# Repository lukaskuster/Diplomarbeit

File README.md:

# P2P GSM-Telephone-Gateway with Client App

### Diploma thesis by [Lukas Kuster](https://github.com/lukaskuster) and [Quentin Wendegass](https://github.com/quentinwendegass) at HTL Mössingerstraße - 4th April 2019

## Table of contents

- [Abstract](#abstract)
  - [Assignment of Tasks](#assignment-of-tasks)
  - [Implementation](#implementation)
  - [Results](#results)
- [Authors](#authors)
- [License](#license)
- [Links](#links)

## Abstract

People that are travelling in foreign countries and still want to be able to use their phone number from their home country, often have to expect huge roaming costs. Because of that, a user-friendly device equipped with the SIM card of the local carrier will be developed, that can then be placed locally in that country. This device will then be able to receive phone calls and SMS via the local carrier and transmit it through a direct Peer-to-peer connection over the internet to the end-user using a client app. Meanwhile the whole process should look and feel like a real, normal call.

### Assignment of Tasks

Because the data transfer rates that accumulate through the voice band streams are relatively big, the transfer has to happen directly between the gateway and the client, with only minimal interaction of a third party (server). The whole system should be designed as easy as possible, so that the setup consists only of starting up the device, quickly running through a setup in the client app and being able to use the gateway instantaneously.

### Implementation

The system basically consists of three components: the gateway, which establishes the calls and SMS messages through its GSM module and the client app, which enables the user to initiate/answer these calls and messages, as well as providing the option to change several settings. In addition, there is a Rendezvous- or Signaling-Server, which initiates the direct peer- to-peer connection between the client and the gateway, as well as the user management of the whole platform which provides the needed scalability.

### Results

The diploma thesis will show, whether such a product is technically as well as economically viable. While working on this project the whole software for such a product as well as a hard- ware prototype will be established.

## Authors

- **Quentin Wendegass** - _Gateway Software & Server_ - [Website](https://wendegass.com)

- **Lukas Kuster** - _Gateway Hardware & iOS-Client_ - [Website](https://lukaskuster.com)

## License

This project is licensed under the GNU Affero General Public License - see the [LICENSE](LICENSE) file for details

## Links

- [iOS-Client: SIMplePhoneKit Documentation](https://lukaskuster.github.io/Diplomarbeit/code-docs/client-ios/) 
- [Gateway: gatewayw Documentation](https://quentinwendegass.github.io/Diplomarbeit/code-docs/gatewayw/html/) 

* [Lukas' repo (@lukaskuster/Diplomarbeit)](https://github.com/lukaskuster/Diplomarbeit)
* [Quentin's repo (@quentinwendegass/Diplomarbeit)](https://github.com/quentinwendegass/Diplomarbeit)

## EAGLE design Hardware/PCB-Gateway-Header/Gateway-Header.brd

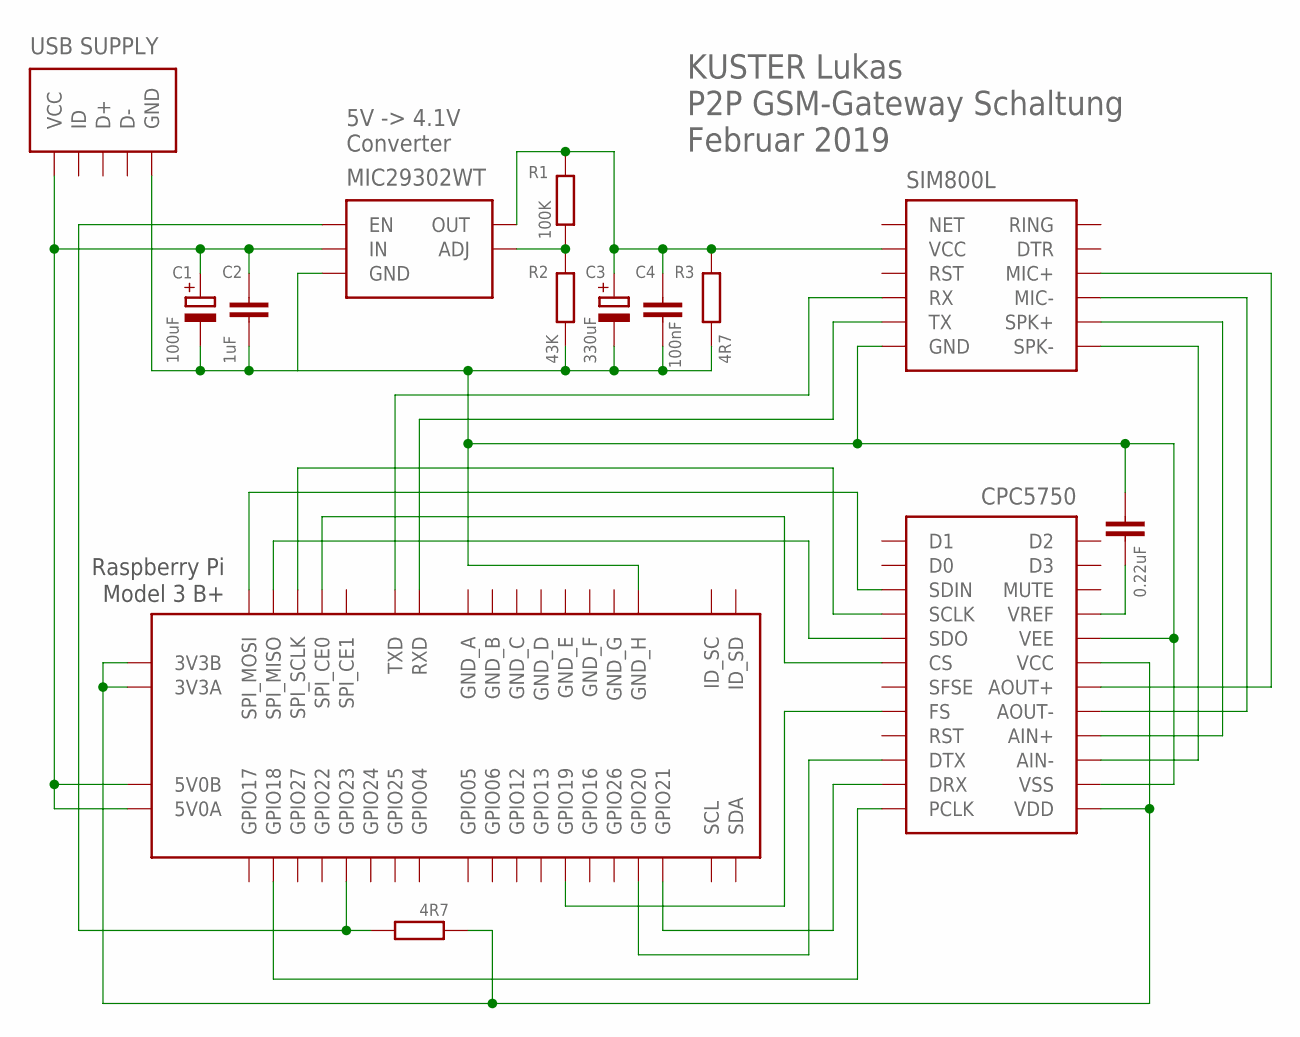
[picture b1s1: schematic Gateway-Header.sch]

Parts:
C: 0.22uF; C025-025X050
C1: 100uF; B45181B
C2: 1uF; C025-025X050
C3: 330uF; B45181B
C4: 100nF; C025-025X050
IC2: MIC29302WT; TO254P483X1022X1511-5P
R1: 100K; 0204/7
R2: 43K; 0204/7
R3, R5: 4R7; 0204/7
U$4: CPC5750
U$5: SIM800LMODULE
U$6: ZX62D-B-5P8-JUNK; ZX62D-B-5P8
X1: RASPI_BOARD_B+#_H; RASPI_BOARD_B+HAT

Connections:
+3.3V: R5.2, U$4.V_CC (VCC), U$4.V_DD (VDD), X1.1 (3V3A), X1.17 (3V3B)
+4V: C3.+, C4.2, IC2.4 (OUT), R1.2, R3.2, U$5.VCC
+5V: C1.+, C2.2, IC2.2 (IN), U$6.P$1 (VCC), X1.2 (5V0A), X1.4 (5V0B)
GND: C.2, C1.-, C2.1, C3.-, C4.1, IC2.3 (GND), R2.1, R3.1, U$4.V_EE (VEE), U$4.V_SS (VSS), U$5.GND, U$6.P$5 (GND), X1.39 (GND_H)
GND_A: X1.6 (GND_A)
GND_B: X1.9 (GND_B)
GND_C: X1.14 (GND_C)
GND_D: X1.20 (GND_D)
GND_E: X1.25 (GND_E)
GND_F: X1.30 (GND_F)
GND_G: X1.34 (GND_G)
unnamed: U$5.RX, X1.8 (TXD)
unnamed: U$5.TX, X1.10 (RXD)
unnamed: IC2.5 (ADJ), R1.1, R2.2
unnamed: U$4.A_IN- (AIN-), U$5.SPK-
unnamed: U$4.A_IN+ (AIN+), U$5.SPK+
unnamed: U$4.A_OUT- (AOUT-), U$5.MIC-
unnamed: U$4.A_OUT+ (AOUT+), U$5.MIC+
unnamed: C.1, U$4.V_REF (VREF)
unnamed: U$4.CS, X1.24 (SPI_CE0)
unnamed: U$4.SCLK, X1.23 (SPI_SCLK)
unnamed: U$4.SDIN, X1.19 (SPI_MOSI)
unnamed: U$4.SDO, X1.21 (SPI_MISO)
unnamed: U$4.PCLK, X1.12 (GPIO18)
unnamed: U$4.D_RX (DRX), X1.40 (GPIO21)
unnamed: U$4.D_TX (DTX), X1.38 (GPIO20)
unnamed: U$4.FS, X1.35 (GPIO19)
unnamed: IC2.1 (EN), R5.1, X1.16 (GPIO23)

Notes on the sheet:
KUSTER Lukas P2P GSM-Gateway Schaltung Februar 2019
5V -> 4.1V Converter

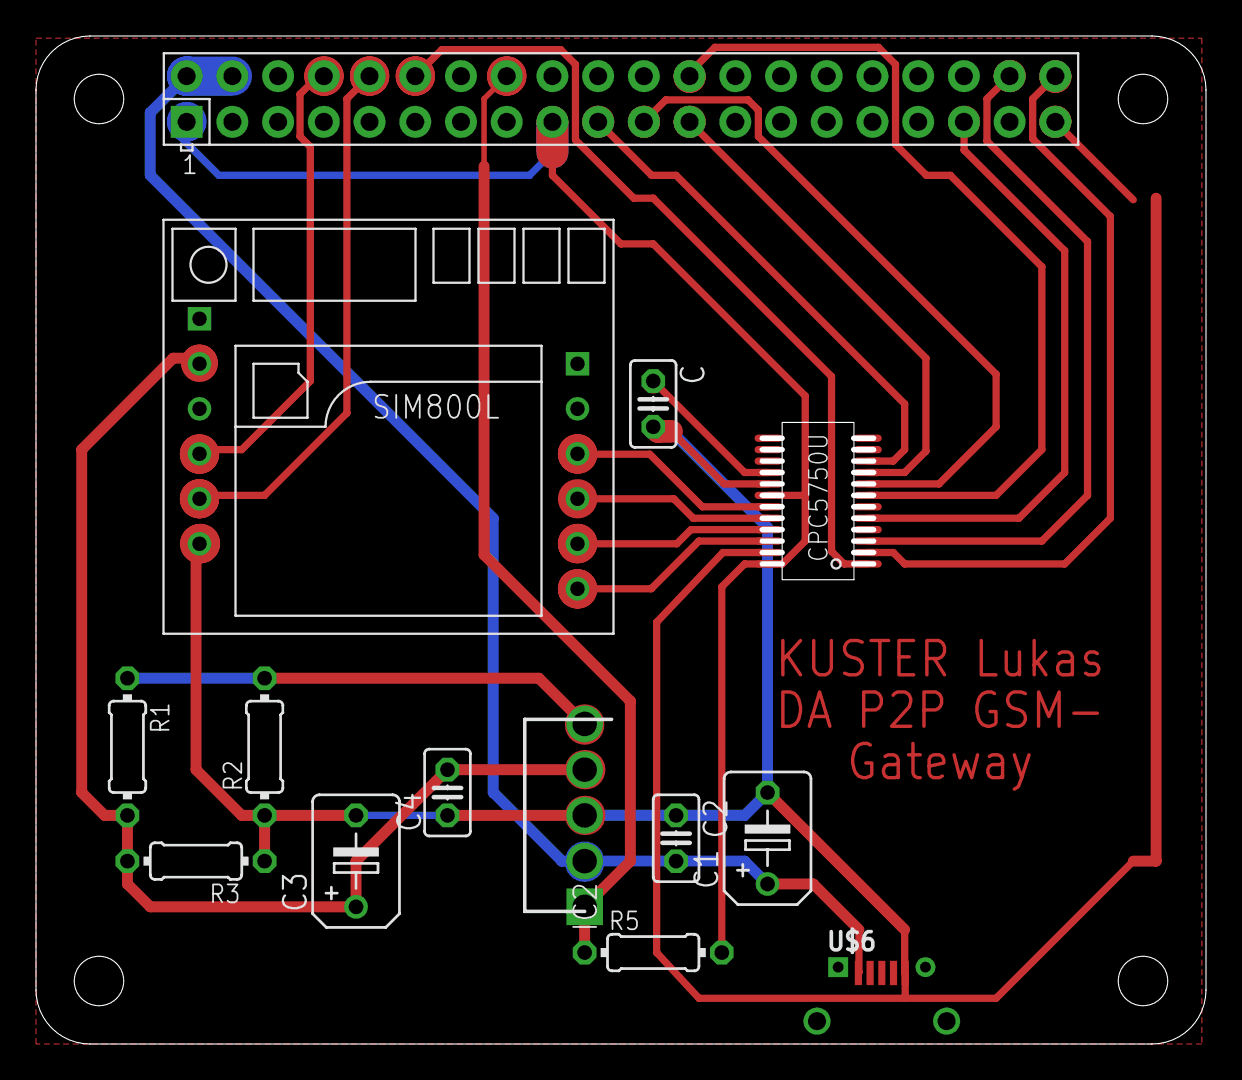
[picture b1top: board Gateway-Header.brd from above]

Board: 2 copper layers, 64.7 x 55.7 mm, 14 parts (0 on the bottom side), 21 nets.

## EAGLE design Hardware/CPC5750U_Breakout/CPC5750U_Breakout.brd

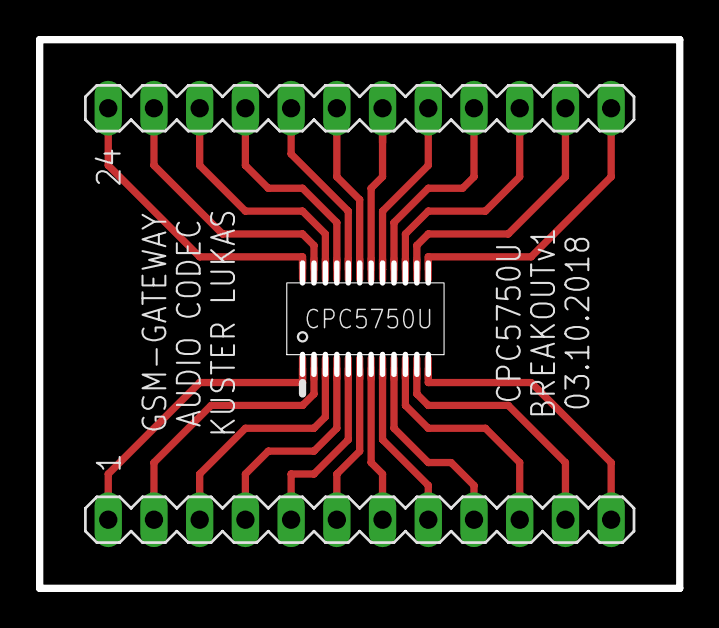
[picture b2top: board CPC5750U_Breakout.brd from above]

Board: 2 copper layers, 35.6 x 30.5 mm, 3 parts (0 on the bottom side), 24 nets.

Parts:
BTM: MA12-1
E$1: CPC5750
TOP: MA12-1

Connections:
S$2: E$1.V_SS, TOP.2
S$3: E$1.A_IN-, TOP.3
S$4: E$1.A_IN+, TOP.4
S$5: E$1.A_OUT-, TOP.5
S$6: E$1.A_OUT+, TOP.6
S$7: E$1.V_CC, TOP.7
S$8: E$1.V_EE, TOP.8
S$9: E$1.V_REF, TOP.9
S$10: E$1.MUTE, TOP.10
S$11: E$1.D3, TOP.11
S$12: E$1.D2, TOP.12
S$13: BTM.1, E$1.PCLK
S$14: BTM.2, E$1.D_RX
S$15: BTM.3, E$1.D_TX
S$16: BTM.4, E$1.RST
S$17: BTM.5, E$1.FS
S$18: BTM.6, E$1.SFSEL
S$19: BTM.7, E$1.CS
S$20: BTM.8, E$1.SDO
S$21: BTM.9, E$1.SCLK
S$22: BTM.10, E$1.SDIN
S$23: BTM.11, E$1.D0
S$24: BTM.12, E$1.D1
S$26: E$1.V_DD, TOP.1

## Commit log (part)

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2018-04-19 added documentation stuff
2018-04-20 adding gantt-diagramm + aufgabestellung
2018-04-20 added docu
2018-04-23 changes to GANTT diagram
2018-04-23 changed documentation
2018-04-26 Adding Presentation
2018-04-26 changes to Dokumentation
2018-09-18 Add server libraries
2018-09-21 Add test script for sim800l module
2018-09-21 Change stuff
2018-09-21 Add Sim800 wrapper class
2018-09-22 Code cleanup and add possibility for custom command
2018-09-24 Close sim module after program finish
2018-09-25 Modify serial connection
2018-09-25 Add name and error message to event
2018-09-26 Split sim800 in different files and create a module
2018-09-26 Fix spelling mistakes
2018-09-26 Switch to pipenv
2018-09-26 Change directory structure
2018-09-26 Add deploy script
2018-09-28 Add support for sending sms
2018-10-02 Add readme
2018-10-03 HW: add CPC5750U breakout board
2018-10-09 client-ios: generate xcode project
2018-10-09 basic UI structure + app icon
2018-10-11 Add SMS-Test
2018-10-11 Fix command to end with ctrl + c
2018-10-11 Caught error when wrong bites get transmitted
2018-10-11 Change host
2018-10-11 Add PdSP-Diagram
2018-10-16 Add signaling-server structure
2018-10-16 Add api template
2018-10-16 Change PdSP chart
2018-10-17 Add authentication
2018-10-18 current app state
2018-10-18 Add signaling server
2018-10-18 Add signaling test
2018-10-18 improvements in voicemail tab / add framework for networking/signalling
2018-10-19 Add database functionality to the signaling server
2018-10-19 Update host
2018-10-19 Add deploy script and change worker filenames
2018-10-19 Code cleanup
2018-10-20 Add gateway endpoint
2018-10-22 Change signaling method
2018-10-22 Add webrtc test with signaling server
2018-10-22 Add gateway api enpoints to paw
2018-10-23 Add api endpoints
2018-10-23 Update response values + put endpoint for gateway
2018-10-23 changes to voicemail functionality / implemented signaling & rtc support (not working yet)
2018-10-24 Fix offer and answer packet
2018-10-24 Fix pip8 errors
2018-10-24 Add error messages
2018-10-24 Add stun server
2018-10-24 rtc setup now possible (RTCClient needs to be redesigned)
2018-10-25 Add logging + bug fixes and code cleanup
2018-10-25 Pip8 fixes
2018-10-25 Add doc comments
2018-10-25 Small code improvements
2018-10-26 Add sse functionality
2018-10-27 Add error handling for failed stream requests
2018-10-27 Change host and add needed header for nginx
2018-10-30 UI tweaks and functionality for ContactTableViewController
2018-10-30 fix iPad crash due to missing property for UIAlertController
2018-11-06 Create Level and AnsiEscapeSequence not in Logger
2018-11-07 SPManager / data models / recent calls view
2018-11-08 Add device endpoints + auth fix
2018-11-08 APIClient: registerDeviceWithServer/getAllGateways
2018-11-09 Update error messages and reformat code
2018-11-09 Add authorization errors
2018-11-09 several API client implementations
2018-11-10 Add authenticate endpoint
2018-11-10 Change response at authentice endpoint
2018-11-10 added authentication logic
2018-11-10 potential fix to iCloud sync problem (issue #6)
2018-11-10 Some improvements and log modules
2018-11-10 Add call module and main entry point
2018-11-12 adds hangUp as pushToGateway Event
2018-11-12 fix local keychain problem when signing in with iCloud
2018-11-12 Sim800 module update + fixes
    + Renamed emitted events to camel case
    + Add ATCommand Class
    + Update ATEvent Class
    + Add sim800 response objects
    + Echo mode can be disables in serial loop
    + Refactored sim800 class to parse response values
2018-11-13 improved login/register ViewController UI also includes register functionality, which still needs some API changes
2018-11-13 removes unused function
2018-11-13 Sync fix
    + new delete /devices endpoint #6
    + fix device return parameters
    + add firstName and lastName arguments to post device
    + Add sync to device #6
2018-11-13 Add async support and response parser
2018-11-13 fixed create account logic after API change (now stable)
2018-11-14 Get imei on first start
2018-11-14 Add new at-commands
2018-11-14 Add cloudUserId
2018-11-15 improvements to iCloud keychain sharing (issue #6)
2018-11-16 Add endpoints for device push notifications
2018-11-19 changed event API endpoint
2018-11-20 Fix apn notifications
2018-11-21 error messages on LoginView
2018-11-21 outsourcing CloudEnvironmentButton
2018-11-22 Implement push notifications for device
2018-11-23 Changes
    + Better WebRTC implementation
    + Signaling timeout fix
    + Add config wrapper
    + Disable echo on sim800 module if it runs in debug mode
    + More small bug fixes
2018-11-24 Fix signaling bug
2018-11-29 Add parser functionality + Code cleanup
2018-11-30 Add ice canditate exchange to gateway
2018-11-30 Optimize for raspberry
2018-12-10 Add caller identification on ring event
2018-12-12 Changes project to use cython
2018-12-12 Adds carrier and firmware version to gateway model
2018-12-12 Uses absolut config path
2018-12-14 Modifies sim800 setup
2018-12-14 Adds scheduler module
2018-12-17 Clean up project
2018-12-17 Add competition applications
2018-12-30 Adds pcm driver
2018-12-30 Fixes config loading bugs
2018-12-30 Changes version to 0.0.3
2018-12-31 Changes char device interface to use 8bit samples
2019-01-01 Adds install scripts
2019-01-01 Adds test for pcm library/driver
2019-01-01 Adds pcm library
2019-01-02 Renames functions and cleans up header
2019-01-02 Changes webrtc to use the pcm wrapper
2019-01-02 Adds possibilities to build the source
2019-01-02 Sets the properly frame length
2019-01-02 Adds requirenments.txt
2019-01-02 Changes version to 0.1.0
2019-01-03 Updates deployment script
2019-01-03 Renames test and fixes Makefile
2019-01-03 Implements split_str() in C
2019-01-03 Removes unused cython declarations
2019-01-04 Fixes webrtc closing bug and optimizes test
2019-01-07 Updates documentation
2019-01-09 Adds color property to gateway
2019-01-09 Further Improvements to Settings View + separate view for name change + set color functionality fully working + order gateway menu button
2019-01-10 more settings UI stuff + disable bouncing on color/name view + grey borders for name textfield + autolayout in colorselector + updated sketch file for icons used
2019-01-10 added TODO file
2019-01-10 added gateway change SIM Pin UI
2019-01-10 total UI support for gateway firmware update
2019-01-14 WebRTC codec selection workaround + move test to specific gateway
2019-01-16 Fixes sim800 bugs
2019-01-16 Changes webrtc to emit errors
2019-01-16 Adds sim800 tests
2019-01-18 Implements voip push notifications
2019-01-19 Adds new push events
2019-01-19 better approach to WebRTC codec selection (still not perfect)
2019-01-19 add select gateway modal on call init in contacts
2019-01-19 adds a lot of CallKit related stuff (incoming calls are now supported and displayed accordingly)
2019-01-20 Implements new events
2019-01-20 fix bug that prevented CallKitManager.reportCallEnded()
2019-01-20 Fixes apn bugs
2019-01-20 lots of changes regarding call handling and a basic Call UI
2019-01-21 fixed PCMAonly bug + deinit peerconnection improvement
2019-01-21 Adds timeout on receiving frame
2019-01-21 Adds dtmf tone support
2019-01-21 Add project website for projects.htl-klu.at
2019-01-21 project website: change from structure.svg to .pdf (font problem)
2019-01-22 Adds implementation and template for answer and hold call
2019-01-22 Fixes bug
2019-01-22 Implements better error handling
2019-01-22 Handles sse errors
2019-01-22 Implements reconnecting to sse server
2019-01-22 Implements reconnect event to notice a connection lost
2019-01-23 add sexy pic of Rodiga
2019-01-25 Adds custom aiortc package to the project
2019-01-25 Fixes logging bug
2019-01-25 Modifies setup to don't use the deprecated dependency_links option
2019-01-25 Removes cython from requirements
2019-01-25 Changes version to 0.1.1
2019-01-25 Updates depoly script
2019-01-30 Fixes typo
2019-01-30 Adds gateway authentication at signaling process
2019-02-01 complete refactor of WebRTCClient & SignalingClient (calls are now working!)
2019-02-01 Fixes bug when no ice candidates are received
2019-02-02 rename SettingsGatewayChangeSIMPinViewController -> GatewaySIMPinViewController
2019-02-02 add FancyBounceVCAnimation (forgot file in commit 0c0669c)
2019-02-02 Adds initial ble setup program
2019-02-02 Adds pcm driver and setup program
2019-02-04 Adds install scripts and modifies deploy script
2019-02-05 Restructures project to setup the build process
2019-02-05 Adds c libs that mistakenly were not commited
2019-02-05 Adds docs for gatewayw
2019-02-06 Adds build script and systemd service units
2019-02-06 Changes script to use environment variables
2019-02-06 Adds installation scripts
2019-02-07 Sets threads in daemon mode
2019-02-07 Updates logging module to use config file
2019-02-07 Adds log config to build
2019-02-08 Adds user service and ble configuration
2019-02-08 Handles check for pin status
2019-02-15 current ble setup state
2019-02-15 fix app icon
2019-03-04 Adds Dialpad (UI & Functionality)
2019-03-05 Recent Calls View Refinements
2019-03-05 getting rid of unused stuff in Contacts View
2019-03-05 visual fix on recent calls view
2019-03-06 syncing SPGateways with Realm
2019-03-06 fix UIAlert popovers on iPad in voicemails
2019-03-06 fix delete voicemail bug
2019-03-06 fix dialpad phone icon tint color
2019-03-06 hide call duration if not even connected in recent calls
2019-03-08 complete refactor of ChatTableViewController (objc -> swift)
2019-03-08 adds UIAlertController when deleting chat
2019-03-14 Fixes bugs and code cleanup
2019-03-14 Changes documentation
2019-03-14 Changes version to 0.2.0
2019-03-14 Updates Readme (second try)
2019-03-27 refactoring to support thesis documentation
2019-04-01 adds jazzy documentation for iOS-Client
2019-04-01 fixing BLE compatibility issues
2019-04-01 fix weekday bug (maybe working idk)
2019-04-01 HW: add gateway header pcb
2019-04-01 cross-referencing each others repository
2019-04-01 change /docs structure
2019-04-01 hide all the html/css stuff to linguist
2019-04-01 fixing mistake that happend while changing docs folder structure
2019-04-01 adds documentation for the ios-client (at least 50%)
2019-04-01 add ios-client doc coverage badge to readme
2019-04-02 Create LICENSE
2019-04-02 Adds gatewayw html doc and code coverage report
2019-04-02 Fixes css loading and coverage build
2019-04-02 rebuild pages
2019-04-02 Adds .nojekyll file to build directory
2019-04-03 Fixes only c99 compatible code
2019-04-03 Adds travis-ci to project
2019-04-03 Lists pigpio as dependency
2019-04-04 Adds delete user endpoint
2019-04-04 Fixes deprecated warning
2019-04-04 Implements api testing
2019-04-04 Caches ffmpeg libs
2019-04-04 Caches ffmpeg binaries
2019-04-04 Caches ffmpeg before installation
2019-04-04 Links api tests with travis
2019-04-04 Enables mongodb service
2019-04-04 Changes travis builds and fixes server test
2019-04-05 Adds gateway endpoint tests + fixes bug
2019-04-05 Add delete account (user) functionality in SPManager
2019-04-05 add build scripts for dependacies
2019-04-05 add ios test target to travis.yml
2019-04-05 fix typo in travis.yml
2019-04-05 change travis xcode version
2019-04-05 Adds api test coverage
2019-04-05 Adds codecov badge
2019-04-07 enable carthage console output (verbose)
2019-04-07 switch to carthage bootstrap
2019-04-07 use github token for travis
2019-04-07 remove compose from travis
2019-04-08 works now?
2019-04-08 wrong log sleep
2019-04-08 try without carthage
2019-04-08 create folder to move to
2019-04-08 there we go
2019-04-08 update travis file
2019-04-08 Cleans up serial loop module
2019-04-09 Implements testing for gatewayw
2019-04-09 Automates documentation deploy to gh-pages
2019-04-09 Changes sphinx version to use hawkmoth
2019-04-09 Adds clang bindings for python
2019-04-12 Increases test coverage and fixes some bugs
